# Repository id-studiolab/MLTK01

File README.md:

# pino_ml5
A toolkit for fast prototyping machine learning experiments build on top of p5.js ml5.js and Arduino, designed and developed by Maria Luce Lupetti and Lorenzo Romagnoli.

Find the full documentation on https://id-studiolab.github.io/MLTK01/

TODO:
- [ ] Add example code on how to integrate with ml5js standard examples
- [ ] Add classification for gestures keeping track of time series
- [ ] Finish writing api

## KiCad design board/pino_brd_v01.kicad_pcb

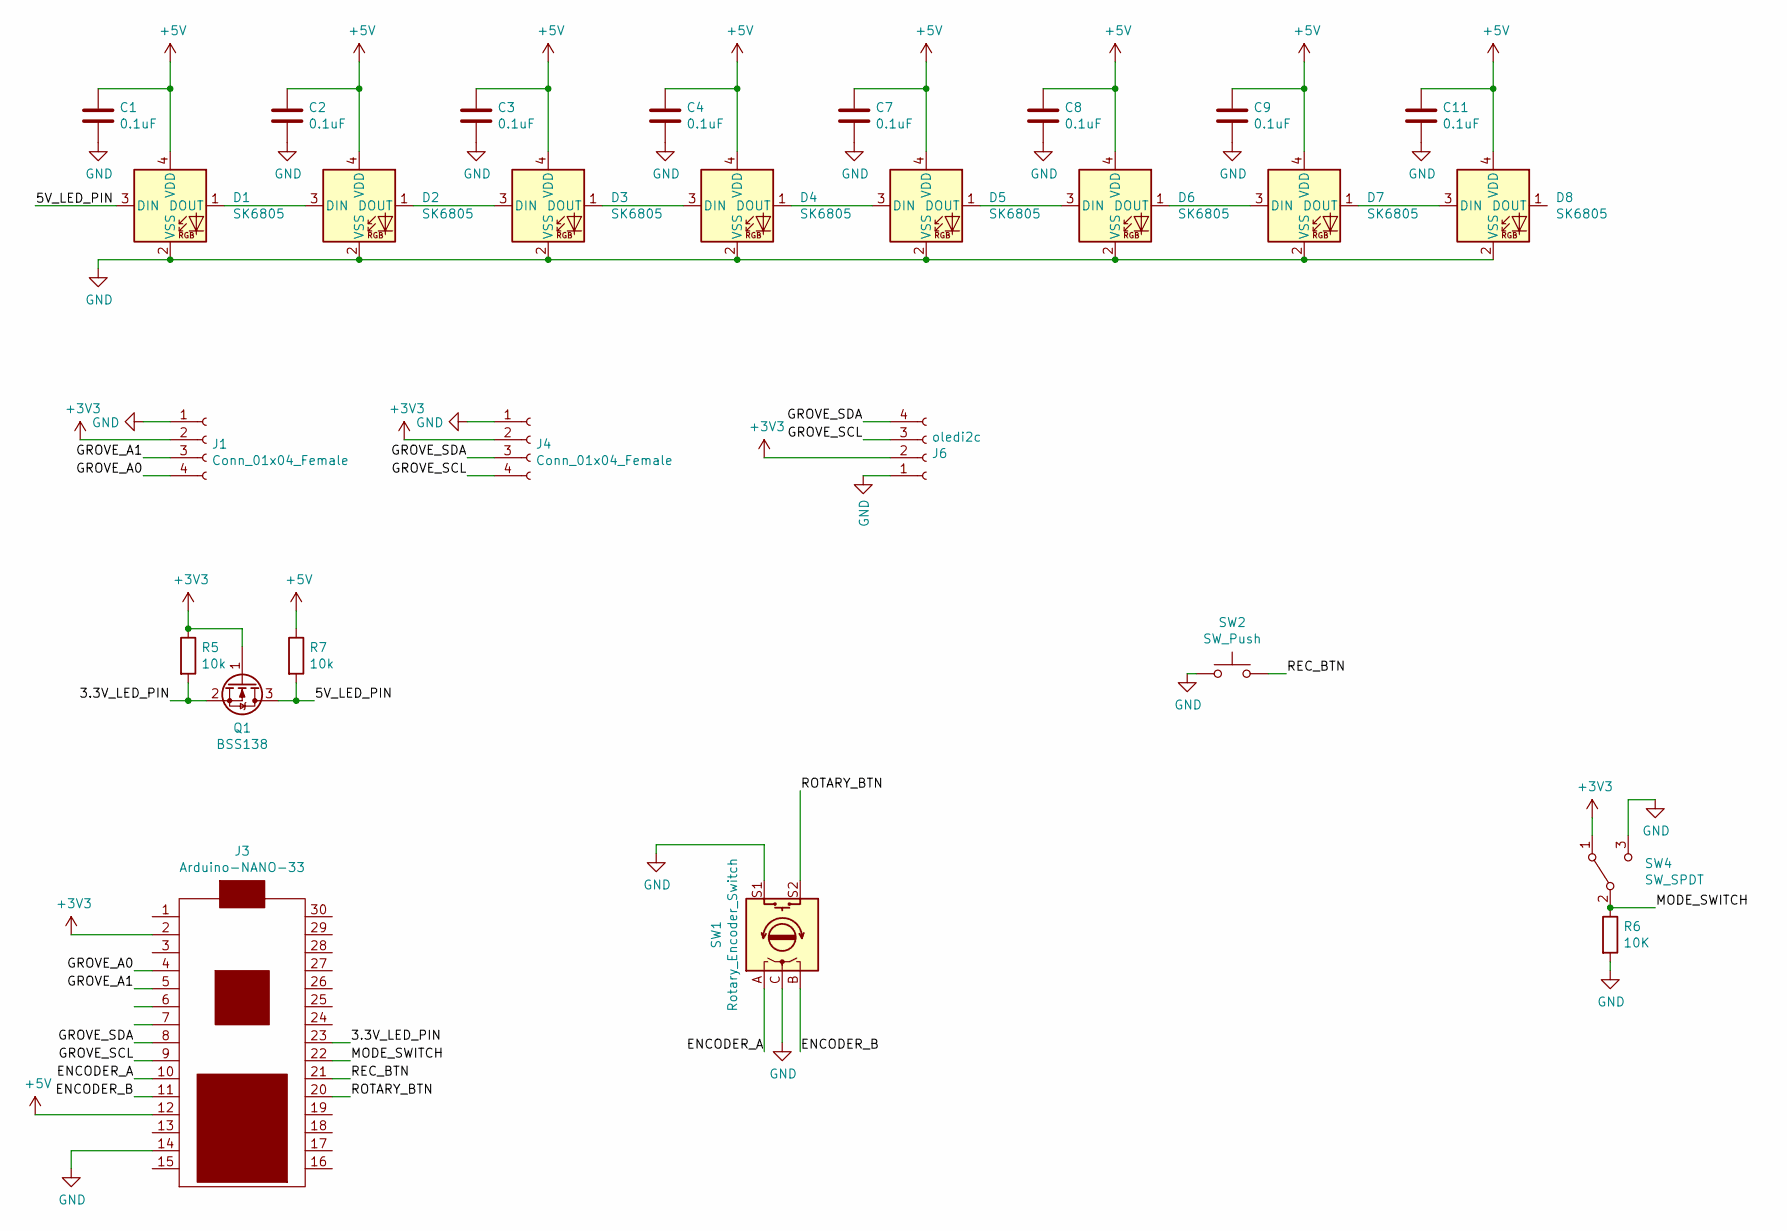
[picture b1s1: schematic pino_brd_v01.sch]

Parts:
C1, C2, C3, C4, C7, C8, C9, C11: 0.1uF; C_0805_2012Metric
D1, D2, D3, D4, D5, D6, D7, D8: SK6805; LED_SK6805_PLCC4_2.4x2.7mm_P1.3mm
J1, J4: Conn_01x04_Female; NS-Tech_Grove_1x04_P2mm_Vertical
J3: Arduino-NANO-33; NANO_33_Footprint_SMD_Castell
J6: oledi2c; PinSocket_1x04_P2.54mm_Vertical
Q1: BSS138; SOT-23
R5, R7: 10k; R_0805_2012Metric
R6: 10K; R_0805_2012Metric
SW1: Rotary_Encoder_Switch; pec11s-953234
SW2: SW_Push; SW_SPST_EVQP0
SW4: SW_SPDT; SW_CuK_JS202011CQN_SCQN_Straight

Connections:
+3V3: J1.2, J3.2, J4.2, J6.2, Q1.1 (G), R5.1, SW4.1 (A)
+5V: C1.1, C2.1, C3.1, C4.1, C7.1, C8.1, C9.1, C11.1, D1.4 (VDD), D2.4 (VDD), D3.4 (VDD), D4.4 (VDD), D5.4 (VDD), D6.4 (VDD), D7.4 (VDD), D8.4 (VDD), J3.12, R7.1
/3.3V_LED_PIN: J3.23, Q1.2 (S), R5.2
/5V_LED_PIN: D1.3 (DIN), Q1.3 (D), R7.2
/ENCODER_A: J3.10, SW1.A
/ENCODER_B: J3.11, SW1.B
/GROVE_A0: J1.4, J3.4
/GROVE_A1: J1.3, J3.5
/GROVE_SCL: J3.9, J4.4, J6.3
/GROVE_SDA: J3.8, J4.3, J6.4
/MODE_SWITCH: J3.22, R6.1, SW4.2 (B)
/REC_BTN: J3.21, SW2.2
/ROTARY_BTN: J3.20, SW1.S2
GND: C1.2, C2.2, C3.2, C4.2, C7.2, C8.2, C9.2, C11.2, D1.2 (VSS), D2.2 (VSS), D3.2 (VSS), D4.2 (VSS), D5.2 (VSS), D6.2 (VSS), D7.2 (VSS), D8.2 (VSS), J1.1, J3.14, J4.1, J6.1, R6.2, SW1.C, SW1.S1, SW2.1, SW4.3 (C)
unnamed: D1.1 (DOUT), D2.3 (DIN)
unnamed: D2.1 (DOUT), D3.3 (DIN)
unnamed: D3.1 (DOUT), D4.3 (DIN)
unnamed: D4.1 (DOUT), D5.3 (DIN)
unnamed: D5.1 (DOUT), D6.3 (DIN)
unnamed: D6.1 (DOUT), D7.3 (DIN)
unnamed: D7.1 (DOUT), D8.3 (DIN)

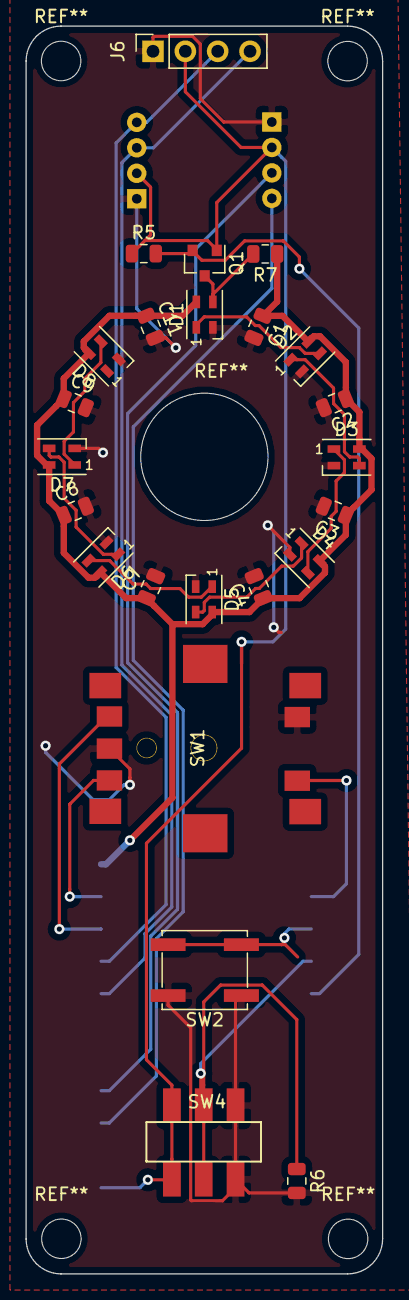
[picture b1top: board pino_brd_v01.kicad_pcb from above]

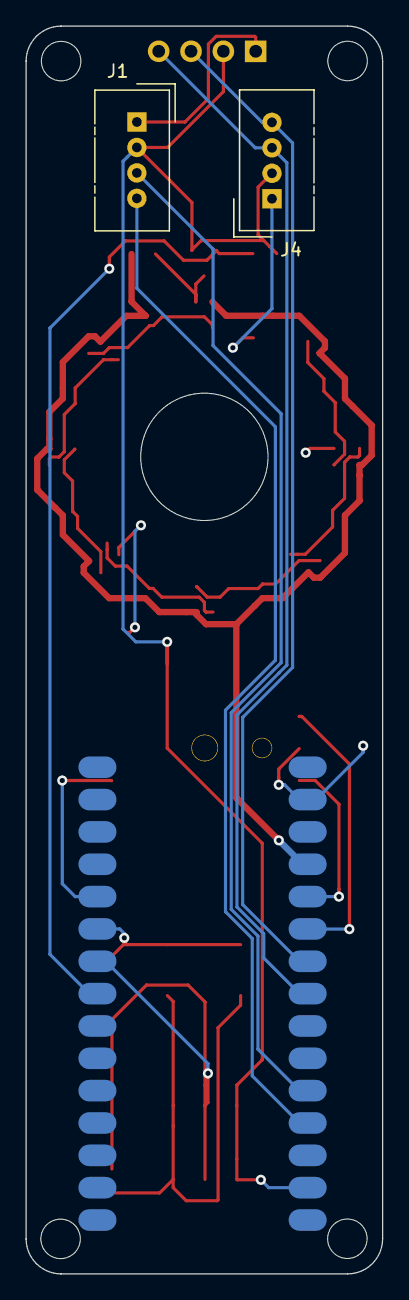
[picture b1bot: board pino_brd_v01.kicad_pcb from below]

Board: 2 copper layers, 28.0 x 98.0 mm, 27 parts (3 on the bottom side), 21 nets.

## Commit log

2020-01-17 converted bleSense code into class
2020-01-17 add function to set rgb ligth
2020-02-21 Set theme jekyll-theme-minimal
2020-03-04 Set theme jekyll-theme-cayman
2020-03-05 Create assets
2020-03-05 Create exercises
2020-03-05 Rename exercises to exercises.md
2020-03-13 refactoring code structure
2020-03-13 restructured folders
2020-03-13 adding 3d models and kicad projct
2020-03-27 added multiple tests code and fixed problem with color reading
2020-03-27 add examples
2020-04-03 added magnetometer example
2020-04-04 add stuff to generate documentation
2020-04-04 created api page
2020-04-04 fixes wrong header
2020-04-04 add example class use to the doc
2020-04-04 improved doc
2020-04-16 written doc for the existing api
2020-04-16 fixes not updated variable name
2020-04-16 add dramastick example
2020-04-16 styled the screen
2020-04-16 initial release
2020-04-16 added an other iframe
2020-04-18 added board schematics
2020-04-18 added board documentation
2020-05-14 adding servo support
2020-07-22 made some edits to the style of the ui + servomotor support
2020-07-22 committing everything ... just in case
2020-07-22 added first draft of the getting started page
2020-07-22 fixes to url related links
2020-07-23 more documentation
2021-07-13 Bump addressable from 2.7.0 to 2.8.0 in /docs
    Bumps [addressable](https://github.com/sporkmonger/addressable) from 2.7.0 to 2.8.0.
    - [Release notes](https://github.com/sporkmonger/addressable/releases)
    - [Changelog](https://github.com/sporkmonger/addressable/blob/main/CHANGELOG.md)
    - [Commits](https://github.com/sporkmonger/addressable/compare/addressable-2.7.0...addressable-2.8.0)
    ---
    updated-dependencies:
2021-11-28 added webcam example
2022-09-01 ready for demo
2022-09-01 updated docs
2022-09-01 added video link
2022-09-01 improved examples doc
2022-09-01 added gifs
2022-09-01 a capo
2022-09-01 fix url
2022-09-01 fix typo
2022-09-01 cleaned examples
2022-10-06 Bump addressable from 2.7.0 to 2.8.1 in /docs
    Bumps [addressable](https://github.com/sporkmonger/addressable) from 2.7.0 to 2.8.1.
    - [Release notes](https://github.com/sporkmonger/addressable/releases)
    - [Changelog](https://github.com/sporkmonger/addressable/blob/main/CHANGELOG.md)
    - [Commits](https://github.com/sporkmonger/addressable/compare/addressable-2.7.0...addressable-2.8.1)
    ---
    updated-dependencies:
2023-01-17 added sketch to support rev2 ble sense
2023-02-01 Bring changes
    bring changes from my fork to this repo
2023-02-02 Update MLTK01Servo.ino
    IDE formatted this version
2023-02-15 clean up getting started text
2023-02-15 remove highlight around code blocks
2023-02-15 add comments to the Sketches
2023-02-16 updated documentation instructions
2023-02-16 Update MLTK01Servo.ino
    Remove color comments related to LED ring
2023-02-16 Update text to reference new version of the board
2023-02-16 Try to regenerate API
2023-02-16 moved the docs creation step to a npm script
2023-02-16 removed gulp dependencies
2023-02-16 bumped node version for githib actions
2023-02-16 try again
2023-02-16 removed git workflows as it is not working
2023-02-16 regenerated docs
2023-03-10 comment out serial things
2023-03-10 bring my examples and work
2023-03-11 work on cleaning up text
2023-03-13 Clean up arduino sketches folder
2023-03-13 separate getting started into arduino setup and tutorial
2023-03-13 Clean up about page
2023-03-13 Update boilerplate html to match tutorial
2023-03-14 Update arduino_setup.md
    Add instructions for next steps
2023-03-23 Finish reviewing tutorial and Boilerplate files
2023-03-23 renumber heading
2023-03-23 Update index.html
    change title
2023-03-23 replace game controller with a commented version
2023-03-23 clean up
2023-03-23 clean up some more
2023-03-23 update dramastick and examples page
2023-03-24 tryng to fix the encoder reliability
2023-03-24 manually regenerated api docs
2023-03-24 Update examples.md
    add color extravaganza
2023-03-24 Update mltk.js
    try to remove write busy
2023-03-24 last minute desperate fix
2023-03-24 fixed issue with Arduino disconnecting after a bit of use
2023-05-12 Add function for microphone data
2023-05-26 use local files for boilerplate
2023-05-26 grammar fix
2023-06-02 clean up code space
2023-06-12 Update mltk.js
    fixed a small bug
2024-05-16 Bump rexml from 3.2.5 to 3.2.8 in /docs
    Bumps [rexml](https://github.com/ruby/rexml) from 3.2.5 to 3.2.8.
    - [Release notes](https://github.com/ruby/rexml/releases)
    - [Changelog](https://github.com/ruby/rexml/blob/master/NEWS.md)
    - [Commits](https://github.com/ruby/rexml/compare/v3.2.5...v3.2.8)
    ---
    updated-dependencies:
2024-08-02 Bump rexml from 3.2.5 to 3.3.3 in /docs
    Bumps [rexml](https://github.com/ruby/rexml) from 3.2.5 to 3.3.3.
    - [Release notes](https://github.com/ruby/rexml/releases)
    - [Changelog](https://github.com/ruby/rexml/blob/master/NEWS.md)
    - [Commits](https://github.com/ruby/rexml/compare/v3.2.5...v3.3.3)
    ---
    updated-dependencies:
